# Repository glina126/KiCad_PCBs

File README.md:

# KiCad_PCBs

All my public PCBs. Some finalized, some still work in progress.

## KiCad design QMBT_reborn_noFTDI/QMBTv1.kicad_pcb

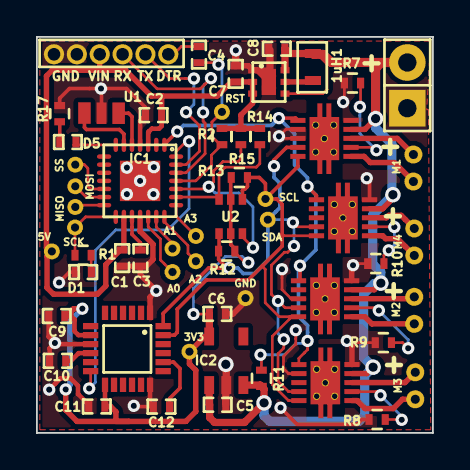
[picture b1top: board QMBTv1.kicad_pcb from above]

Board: 2 copper layers, 22.0 x 22.0 mm, 57 parts (0 on the bottom side), 43 nets.

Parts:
1uH1: INDUCTOR; Inductor_0603
C1, C2, C3, C4, C10, C11: 0.1uF; SMD-0402_c
C5: 1uF; SMD-0402_c
C6, C8: 2.2uF; SMD-0402_c
C7: 4.7uF; SMD-0402_c
C9: 10nF; SMD-0402_c
C12: 2.2nF; SMD-0402_c
C13: 6pin_1.27mm
D1, D5: LED; SMD-0402_LED
IC1: ATMEGA328P-MM; QFN-28-4x4mm_fixed_mask
IC2: MCP1802_(Vreg); Sot-23-5
IC3: Booster_5V; FAN4860
IC4: MPU6050
P1: M3; 2x0.5mm_Through_Hole
P2: M1; 2x0.5mm_Through_Hole
P3: M4; 2x0.5mm_Through_Hole
P4: M2; 2x0.5mm_Through_Hole
P5: A0; 1x0.5mm_Through_hole2
P6: A1; 1x0.5mm_Through_hole2
P7: A2; 1x0.5mm_Through_hole2
P8: A3; 1x0.5mm_Through_hole2
P9: MISO; 1x0.5mm_Through_hole2
P10: MOSI; 1x0.5mm_Through_hole2
P11: SCK; 1x0.5mm_Through_hole2
P12: RST; 1x0.5mm_Through_hole2
P14: SDA; 1x0.5mm_Through_hole2
P15: SCL; 1x0.5mm_Through_hole2
P16: SS; 1x0.5mm_Through_hole2
P17: VCC; Socket_Strip_Straight_1x02
P18: 3V3; 1x0.5mm_Through_hole2
P19: GND; 1x0.5mm_Through_hole2
P20: 5V; 1x0.5mm_Through_hole2
R1, R12, R13, R14, R15, R17: 1K; R_0402
R2: 10K; R_0402
R7, R8, R9, R10: 0.22ohm; R_0402
R11: 10Kohm; R_0402
U1: ceramic_resonator; ceramic_resonator_smd
U2: BSS138DW_array
U3, U4, U5, U6: DRV8830

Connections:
+3.3V: C6.1, C9.1, C11.1, IC2.5, IC4.8, IC4.13, P18.1, R12.1, R13.1, U2.2, U2.5
+5V: C1.1, C2.1, C7.1, C13.3, IC1.3, IC1.16, IC3.2, IC3.3, P20.1, R2.1, R14.1, R15.1
/MotorIC/out1-m1: P2.1, U3.3
/MotorIC/out1-m2: P4.1, U5.3
/MotorIC/out1-m3: P1.1, U4.3
/MotorIC/out1-m4: P3.1, U6.3
/MotorIC/out2-m1: P2.2, U3.1
/MotorIC/out2-m2: P4.2, U5.1
/MotorIC/out2-m3: P1.2, U4.1
/MotorIC/out2-m4: P3.2, U6.1
A0: IC1.19, P5.1
A1: IC1.20, P6.1
A2: IC1.21, P7.1
A3: IC1.22, P8.1
D3: IC1.1, R11.2, U3.6, U4.6, U5.6, U6.6
D5: D5.1, IC1.7
D10: IC1.12, P16.1
DTR: C4.1, C13.6
GND: C1.2, C2.2, C3.2, C5.2, C6.2, C7.2, C8.2, C9.2, C10.2, C11.2, C12.2, C13.1, C13.2, D1.2, IC1.4, IC1.18, IC1.29, IC2.2, IC3.1, IC3.7, IC4.1, IC4.9, IC4.18, P17.1, P19.1, R7.1, R8.1, R9.1, R10.1, R17.1, U1.3, U3.5, U3.7, U3.8, U3.11, U4.5, U4.7, U4.11, U5.5, U5.8, U5.11, U6.5, U6.11
H_SCL: IC1.24, R15.2, U2.6
H_SDA: IC1.23, R14.2, U2.3
INT: IC1.28, IC4.12
MISO: IC1.14, P9.1
MOSI: IC1.13, P10.1
unnamed: 1uH1.1, IC3.5
unnamed: C3.1, IC1.17
unnamed: C10.1, IC4.10
unnamed: C12.1, IC4.20
unnamed: D1.1, R1.1
unnamed: D5.2, R17.2
unnamed: IC1.5, U1.1
unnamed: IC1.6, U1.2
unnamed: R7.2, U3.2
unnamed: R8.2, U4.2
unnamed: R9.2, U5.2
unnamed: R10.2, U6.2
RESET: C4.2, IC1.25, P12.1, R2.2
RXI: C13.4, IC1.26
SCK: IC1.15, P11.1, R1.2
SCL: IC4.23, P15.1, R13.2, U2.1, U3.10, U4.10, U5.10, U6.10
SDA: IC4.24, P14.1, R12.2, U2.4, U3.9, U4.9, U5.9, U6.9
TXD: C13.5, IC1.27
VIN: 1uH1.2, C5.1, C8.1, IC2.1, IC2.3, IC3.4, IC3.6, P17.2, R11.1, U3.4, U4.4, U5.4, U6.4

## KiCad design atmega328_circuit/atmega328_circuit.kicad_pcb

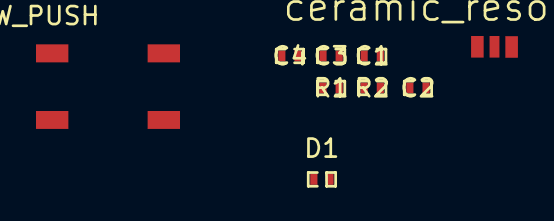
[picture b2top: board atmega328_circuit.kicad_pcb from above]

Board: 2 copper layers, 9 parts (0 on the bottom side), 4 nets, no tracks yet.

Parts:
C1, C2, C3, C4: C; SMD-0402_c
D1: LED; SMD-0402_LED
R1, R2: R; SMD-0402_r
SW1: SW_PUSH; switch_tactile_SM10
U1: ceramic_resonator; ceramic_resonator_smd

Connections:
+5V: C1.1, C2.1, R2.1
GND: C1.2, C2.2, C3.2, D1.2, SW1.2, U1.3
unnamed: D1.1, R1.1
RESET: C4.2, R2.2, SW1.1

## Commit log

2015-02-22 initial commit.
